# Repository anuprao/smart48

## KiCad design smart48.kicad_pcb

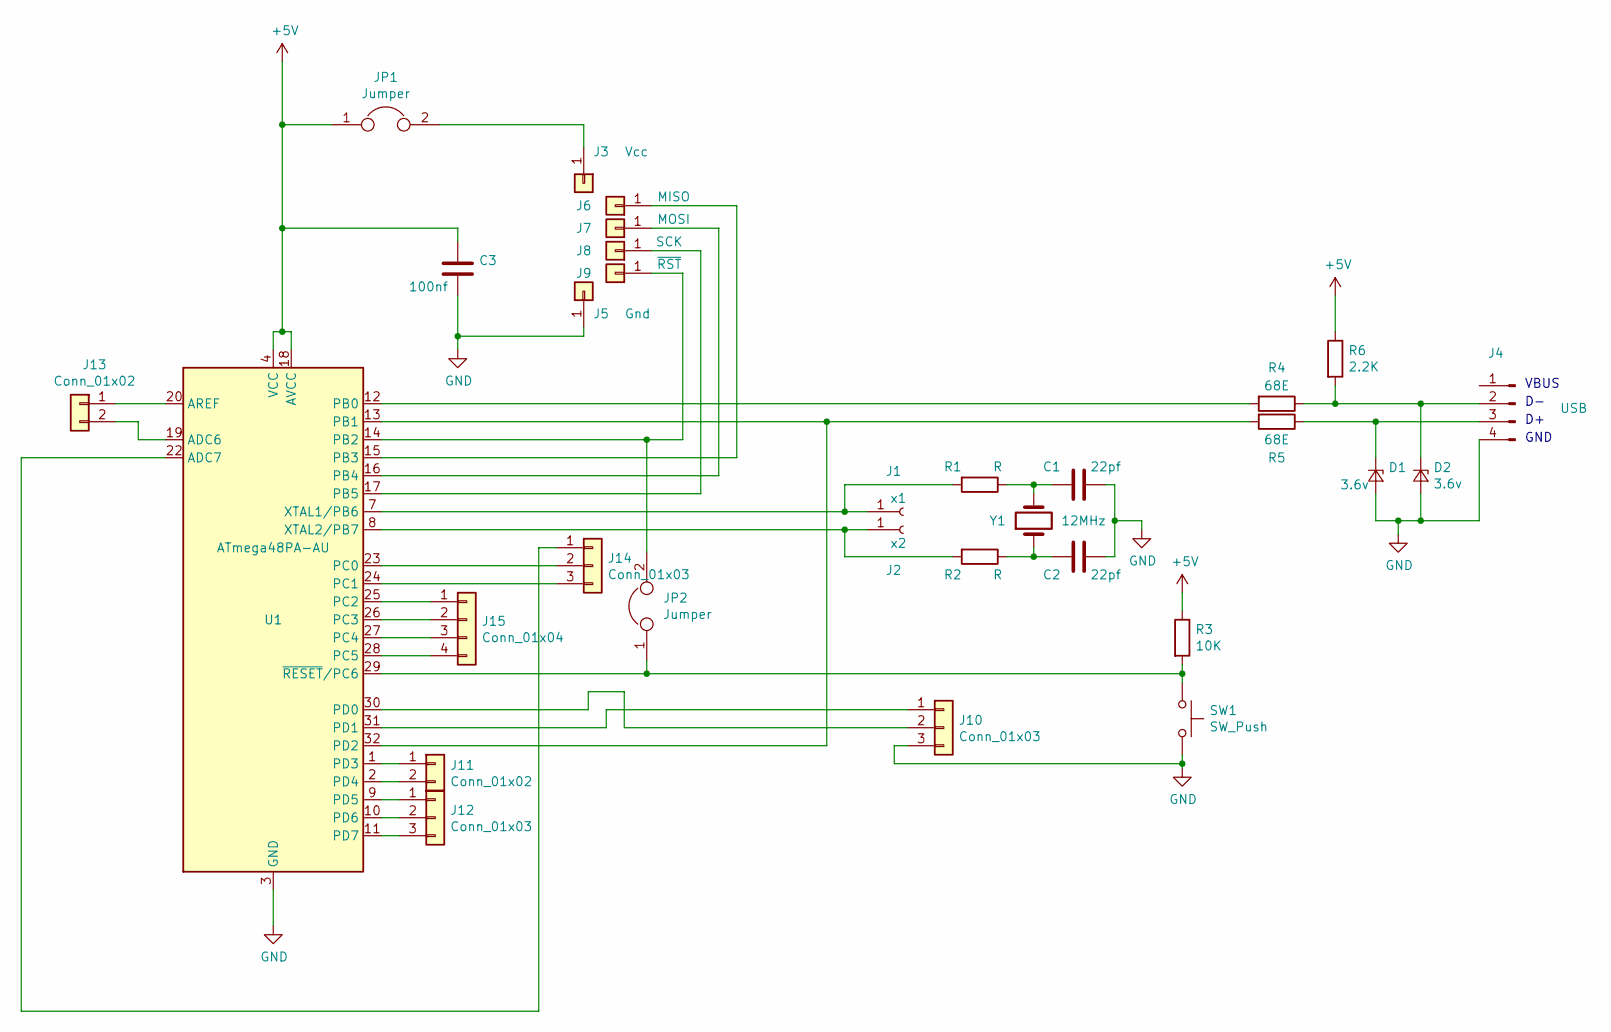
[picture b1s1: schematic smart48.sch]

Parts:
C1, C2: 22pf; C_Disc_D3.0mm_W2.0mm_P2.50mm
C3: 100nf; C_Disc_D3.0mm_W2.0mm_P2.50mm
D1, D2: 3.6v; R_Axial_DIN0207_L6.3mm_D2.5mm_P2.54mm_Vertical
J1: x1; PinHeader_1x01_P2.54mm_Vertical
J2: x2; PinHeader_1x01_P2.54mm_Vertical
J3: Vcc; PinHeader_1x01_P2.54mm_Vertical
J4: USB; PinSocket_1x04_P2.54mm_Vertical
J5: Gnd; PinHeader_1x01_P2.54mm_Vertical
J6: MISO; PinHeader_1x01_P2.54mm_Vertical
J7: MOSI; PinHeader_1x01_P2.54mm_Vertical
J8: SCK; PinHeader_1x01_P2.54mm_Vertical
J9: ~RST; PinHeader_1x01_P2.54mm_Vertical
J10, J12, J14: Conn_01x03; PinHeader_1x03_P2.54mm_Vertical
J11, J13: Conn_01x02; PinHeader_1x02_P2.54mm_Vertical
J15: Conn_01x04; PinHeader_1x04_P2.54mm_Vertical
JP1, JP2: Jumper; R_Axial_DIN0207_L6.3mm_D2.5mm_P2.54mm_Vertical
R1, R2: R; R_Axial_DIN0207_L6.3mm_D2.5mm_P2.54mm_Vertical
R3: 10K; R_Axial_DIN0207_L6.3mm_D2.5mm_P2.54mm_Vertical
R4, R5: 68E; R_Axial_DIN0207_L6.3mm_D2.5mm_P2.54mm_Vertical
R6: 2.2K; R_Axial_DIN0207_L6.3mm_D2.5mm_P2.54mm_Vertical
SW1: SW_Push; R_Axial_DIN0207_L6.3mm_D2.5mm_P2.54mm_Vertical
U1: ATmega48PA-AU; TQFP-32_7x7mm_P0.8mm
Y1: 12MHz; Crystal_HC50_Vertical

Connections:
+5V: C3.1, JP1.1, R3.1, R6.1, U1.4 (VCC), U1.6 (VCC), U1.18 (AVCC)
GND: C1.1, C2.1, C3.2, D1.2 (A), D2.2 (A), J4.4, J5.1, J10.3, SW1.2, U1.3 (GND), U1.5 (GND), U1.21 (GND)
unnamed: C1.2, R1.1, Y1.2
unnamed: C2.2, R2.1, Y1.1
unnamed: D1.1 (K), J4.3, R5.1
unnamed: D2.1 (K), J4.2, R4.1, R6.2
unnamed: J1.1, R1.2, U1.7 (XTAL1/PB6)
unnamed: J2.1, R2.2, U1.8 (XTAL2/PB7)
unnamed: J3.1, JP1.2
unnamed: J6.1, U1.15 (PB3)
unnamed: J7.1, U1.16 (PB4)
unnamed: J8.1, U1.17 (PB5)
unnamed: J9.1, JP2.2, U1.14 (PB2)
unnamed: J10.1, U1.31 (PD1)
unnamed: J10.2, U1.30 (PD0)
unnamed: J11.1, U1.1 (PD3)
unnamed: J11.2, U1.2 (PD4)
unnamed: J12.1, U1.9 (PD5)
unnamed: J12.2, U1.10 (PD6)
unnamed: J12.3, U1.11 (PD7)
unnamed: J13.1, U1.20 (AREF)
unnamed: J13.2, U1.19 (ADC6)
unnamed: J14.1, U1.22 (ADC7)
unnamed: J14.2, U1.23 (PC0)
unnamed: J14.3, U1.24 (PC1)
unnamed: J15.1, U1.25 (PC2)
unnamed: J15.2, U1.26 (PC3)
unnamed: J15.3, U1.27 (PC4)
unnamed: J15.4, U1.28 (PC5)
unnamed: JP2.1, R3.2, SW1.1, U1.29 (~RESET~/PC6)
unnamed: R4.2, U1.12 (PB0)
unnamed: R5.2, U1.13 (PB1), U1.32 (PD2)

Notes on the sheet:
GND
VBUS

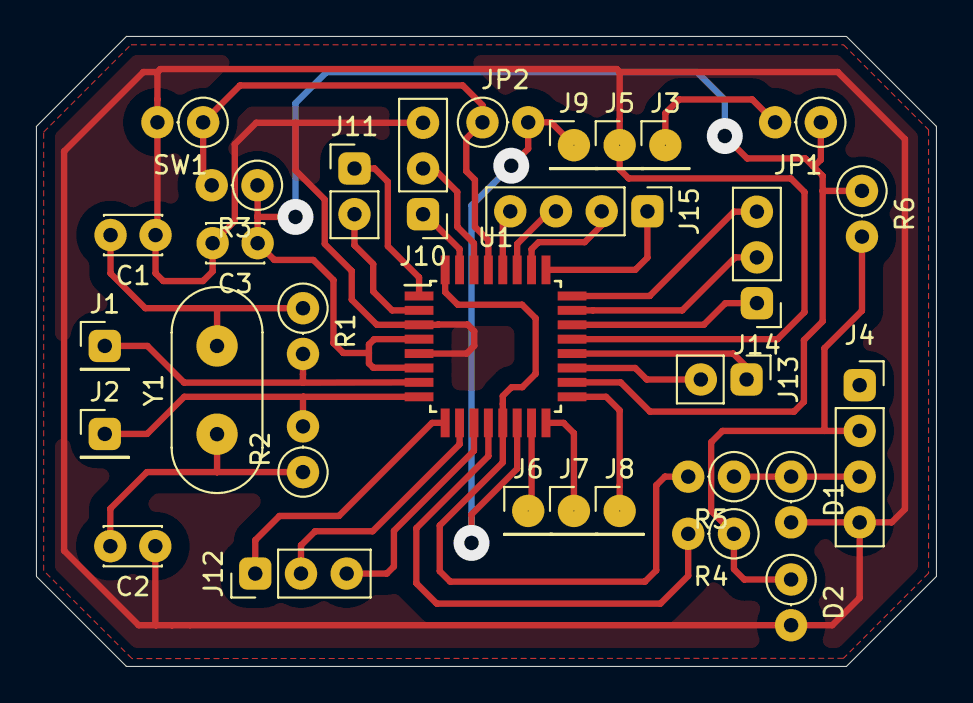
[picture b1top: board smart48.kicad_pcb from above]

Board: 2 copper layers, 50.0 x 35.0 mm, 31 parts (0 on the bottom side), 32 nets.

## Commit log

2020-03-14 General purpose Smart48 board using PTH compinents
